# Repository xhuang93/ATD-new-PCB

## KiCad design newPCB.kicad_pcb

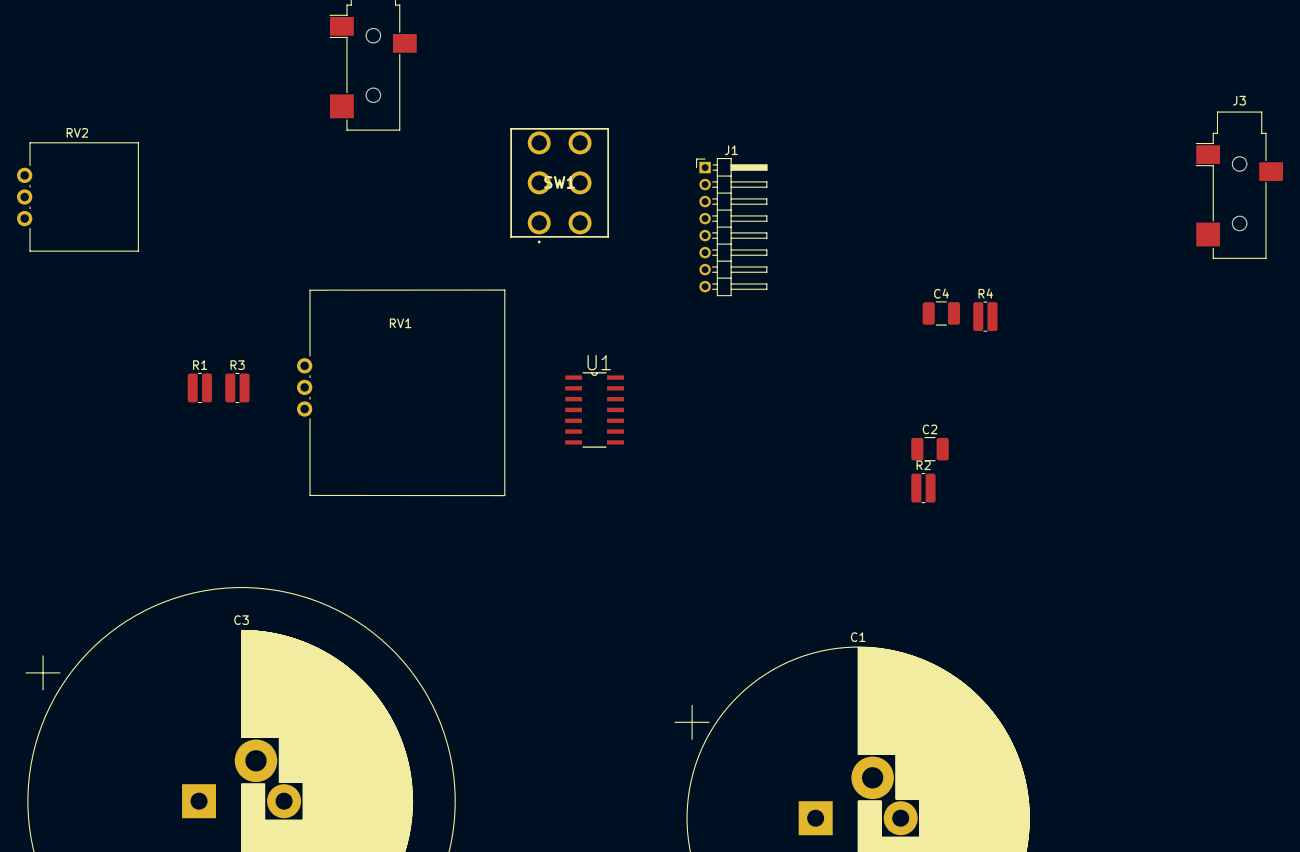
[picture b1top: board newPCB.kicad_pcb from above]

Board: 2 copper layers, 15 parts (0 on the bottom side), 15 nets, no tracks yet.

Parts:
C1, C3: 260u; CP_Radial_D40.0mm_P10.00mm_3pin_SnapIn
C2, C4: 820p; C_1210_3225Metric_Pad1.42x2.65mm_HandSolder
J1: Conn_01x08_Male; PinHeader_1x08_P2.00mm_Horizontal
J2, J3: AudioJack3; Jack_3.5mm_CUI_SJ-3523-SMT_Horizontal
R1, R3: 10k; R_0612_1632Metric_Pad1.18x3.40mm_HandSolder
R2, R4: 2.49M; R_0612_1632Metric_Pad1.18x3.40mm_HandSolder
RV1, RV2: 500k; Potentiometer_Vishay_148-149_Single_Vertical
SW1: SW_Push_DPDT; MS23BNW03
U1: TL084; SOIC127P600X175-14N

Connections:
+9V: SW1.1, U1.4
-9V: SW1.4, U1.11
GND: J1.3, J1.4, J2.S, J3.S, U1.2, U1.6
unnamed: C1.1, C2.2, R2.2, U1.3
unnamed: C1.2, R1.1
unnamed: C2.1, J1.5, R2.1, U1.1
unnamed: C3.1, C4.2, R4.2, U1.5
unnamed: C3.2, R3.1
unnamed: C4.1, J1.6, R4.1, U1.7
unnamed: J1.1, SW1.2
unnamed: J1.2, SW1.5
unnamed: J2.R, J2.T, RV1.2
unnamed: J3.R, J3.T, RV2.2
unnamed: R1.2, RV1.1
unnamed: R3.2, RV2.1

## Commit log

2022-02-22 Just adding personal notes file -Owen
2022-02-26 updated personal notes, added datasheet for op amp tl084
2022-02-27 Made heirarchical structure, replaced tl084 with tl081, still needs work
2022-03-07 Added bypass capacitors to newPCBamps layer, need to implement analog ground in top layer
